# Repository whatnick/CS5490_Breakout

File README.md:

# CS5490 Breakout

Breakout board for breadboard testing using the [CS5490](https://www.cirrus.com/products/cs5490/) Energy Monitor ASIC from Cirrus Logic.

## Where to get the board

The board can be obtained on:
- [Tindie](https://www.tindie.com/products/whatnick/cs5490-breakout/)
- [Aisler](https://aisler.net/p/VEGOWUSS)
- [OSHPark](https://oshpark.com/shared_projects/b8ShL1WJ)
- [PCBWay](https://www.pcbway.com/project/shareproject/CS5490_Breakout.html)

## Board Images

**Top Render**

**Bottom Render**

## Software Support

- [Arduino Library](https://github.com/tiagolobao/CS5490)
- [Micropython/Python Notebook](https://github.com/whatnick/cs5490_micropython)

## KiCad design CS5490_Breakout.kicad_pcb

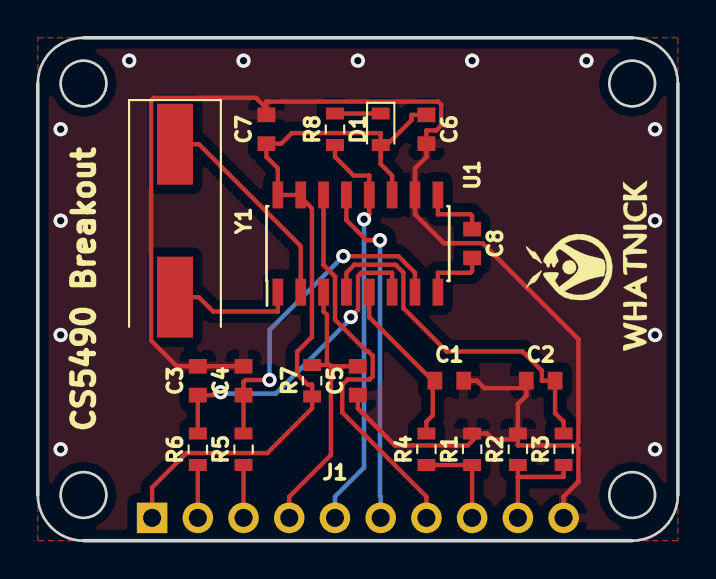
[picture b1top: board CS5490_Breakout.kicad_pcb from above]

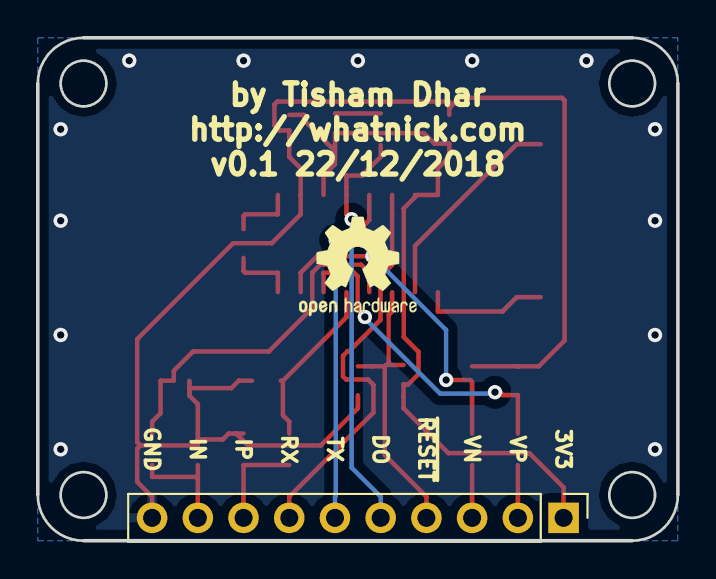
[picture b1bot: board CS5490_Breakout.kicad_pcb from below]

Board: 2 copper layers, 35.6 x 27.9 mm, 22 parts (2 on the bottom side), 19 nets.

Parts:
C1, C2, C3, C4: 27nF; C_0603_1608Metric
C5, C6, C7, C8: 100nF; C_0603_1608Metric
D1: LED; LED_0603_1608Metric
G1: LOGO; Whatnick_logo
J1: Conn_01x10; PinHeader_1x10_P2.54mm_Vertical
LOGO1: Logo_Open_Hardware_Small; OSHW-Logo2_7.3x6mm_SilkScreen
R1, R2: 2.4R; R_0603_1608Metric
R3, R4, R5, R6, R8: 1K; R_0603_1608Metric
R7: 10K; R_0603_1608Metric
U1: CS5490-ISZ; SOIC-16_3.9x9.9mm_P1.27mm
Y1: 4.096MHz; Crystal_SMD_HC49-SD

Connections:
+3V3: C6.2, C7.1, D1.2, J1.1, R7.2, U1.11, U1.15, U1.16
DO: J1.5, R8.2, U1.12
GND: C1.2, C2.1, C3.2, C4.1, C5.1, C6.1, C7.2, J1.10, R1.1, R2.2, U1.10
IIN+: C1.1, R4.1, U1.5
IIN-: C2.2, R3.1, U1.4
IN: J1.9, R2.1, R3.2
IP: J1.8, R1.2, R4.2
unnamed: C8.1, U1.9
unnamed: C8.2, U1.8
unnamed: D1.1, R8.1
unnamed: U1.1, Y1.2
unnamed: U1.2, Y1.1
RX: J1.7, U1.14
TX: J1.6, U1.13
VIN+: C3.1, R6.1, U1.6
VIN-: C4.2, R5.1, U1.7
VN: J1.3, R5.2
VP: J1.2, R6.2
~RESET: C5.2, J1.4, R7.1, U1.3

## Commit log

2018-12-20 Initial import
2018-12-22 Complete place and route
2018-12-22 Ignore auto-route files
2018-12-22 Generate Gerbers
2018-12-22 Added BOM files
2019-04-19 Move connector closer
2019-12-31 Add BOM and render experiments from Kicon 2019
2020-05-16 Added README details and BOM
